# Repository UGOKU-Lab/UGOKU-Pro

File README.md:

# UGOKU One
UGOKU Pro のハードウェア設計データ（KiCADデータ）のリポジトリです。

UGOKU Pro はモータやセンサを使ったロボットなどのアプリケーションを少しでも手軽にテスト、制御することを目的に開発している汎用基板です。

広く普及しているマイコンボードや無線モジュールに加え、高出力なDCモータドライバを2個搭載しています。さらに、汎用IOポートを設け幅広いアプリケーションに対応します。
Androidアプリ[FlexConsole](https://github.com/UGOKU-Lab/FlexConsole_for_Bluetooth_Serial)と組み合わせることでスマートフォンから手軽に遠隔操作や監視が行えます。

[](

)

| 主要搭載部品 |  |
----|---- 
| マイコンボード | Nucleo-F303K8 | 
| 無線モジュール | ESP32-WROOM-32E |
| DCモータドライバ | 2× TB67H303HG |
| CANトランシーバ | MCP2562-E/SN |

# 使用ライブラリ
[SnapMagic](https://www.snapeda.com/home/) よりダウンロードしたKiCADのライブラリ（CC BY-SA）を使用しています

# ライセンス
<br />この データ は <a rel="license" href="http://creativecommons.org/licenses/by-sa/4.0/deed.ja">クリエイティブ・コモンズ 表示 4.0 国際 ライセンス</a>の下に提供されています。

本データおよび本データにより製作した基板は良識の範囲で自由に非営利、営利問わず使用できます。また、改変、再配布も可能です。
ただし、再配布の際には本リポジトリのリンクを掲載を希望します。（本プロジェクトの目的に即した改良についてはプルリクエストを歓迎します）。  
また、本データにより生じた損害等の一切の責任を負いかねますので、ご了承ください。

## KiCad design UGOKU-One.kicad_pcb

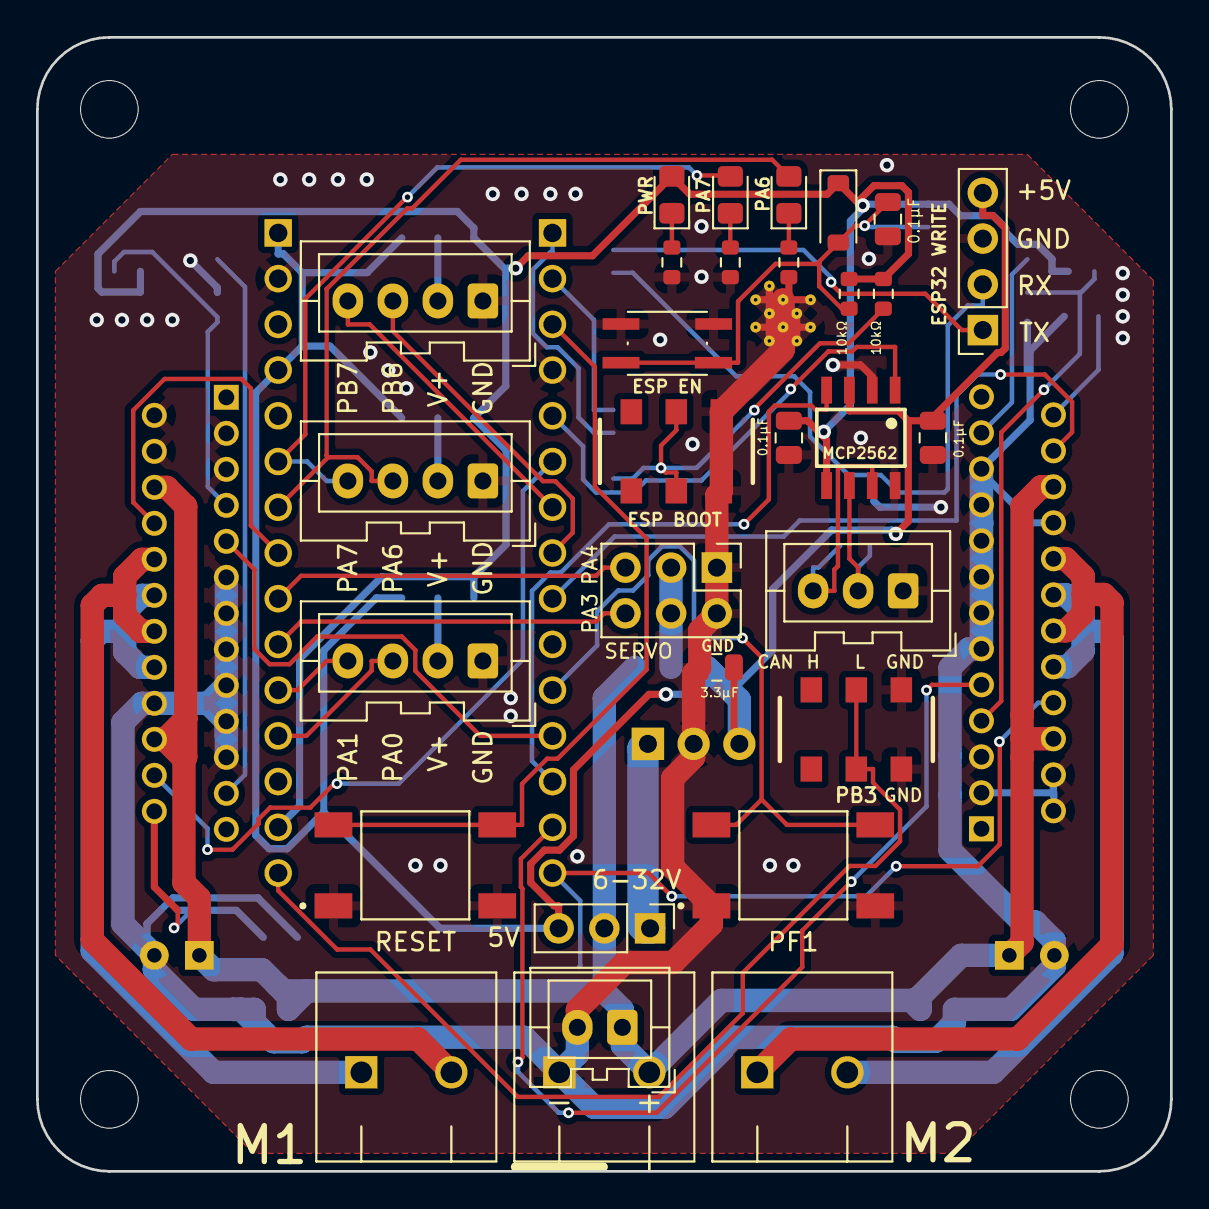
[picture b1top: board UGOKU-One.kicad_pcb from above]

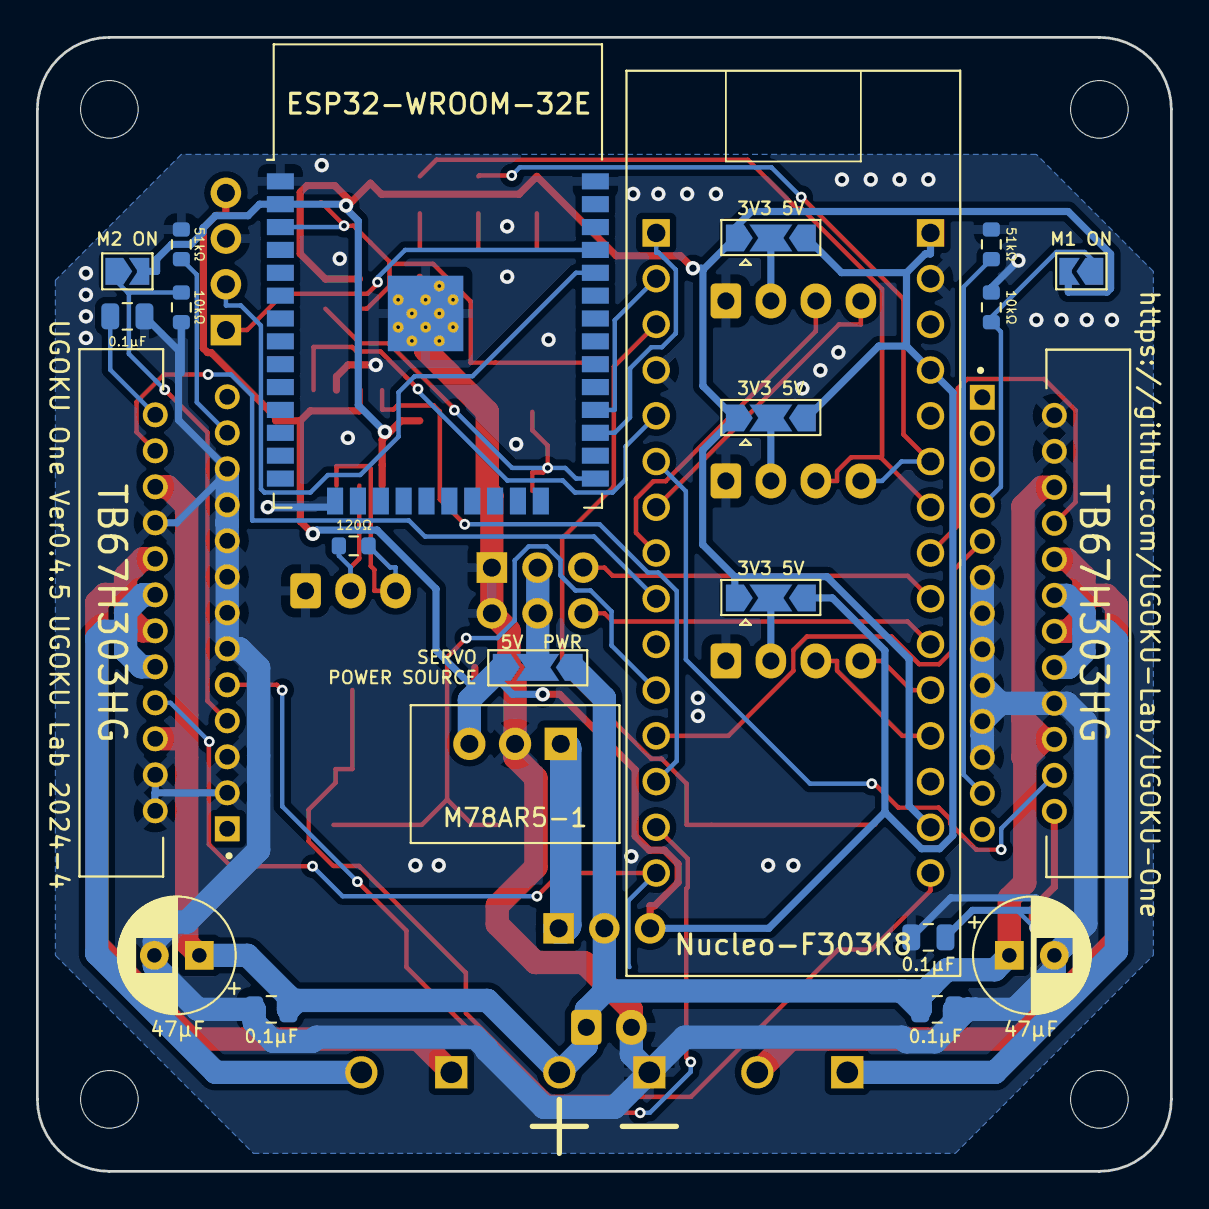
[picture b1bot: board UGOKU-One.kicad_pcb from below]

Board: 2 copper layers, 63.0 x 63.0 mm, 56 parts (22 on the bottom side), 49 nets.

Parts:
C1, C2, C3, C4, C9, C11, C13: 0.1μF; C_0805_2012Metric
C5, C12: 47μF; CP_Radial_D6.3mm_P2.50mm
C10: 3.3μF; C_0805_2012Metric
CN1, CN2, CN3: Conn_01x04; JST_XA_B04B-XASK-1_1x04_P2.50mm_Vertical
CN4: CAN; JST_XA_B03B-XASK-1_1x03_P2.50mm_Vertical
D1: D; D_SOD-123
J2: Conn_02x03_Odd_Even; PinHeader_2x03_P2.54mm_Vertical
J3: Conn_01x02_Male; JST_XA_B02B-XASK-1_1x02_P2.50mm_Vertical
J4: PA10; PinHeader_1x03_P2.54mm_Vertical
J6: Conn_01x04; PinSocket_1x04_P2.54mm_Vertical
JP1, JP2, JP3, JP4: Jumper_NC_Dual; SolderJumper-3_P2.0mm_Open_TrianglePad1.0x1.5mm
L1: PWR; LED_0805_2012Metric_Pad1.15x1.40mm_HandSolder
L2, L3: LED; LED_0805_2012Metric_Pad1.15x1.40mm_HandSolder
MH1, MH2, MH3, MH4: MountingHole_3.2mm_M3
MJP1, MJP2: Jumper; SolderJumper-2_P1.3mm_Open_TrianglePad1.0x1.5mm
R1: 120Ω; R_0603_1608Metric
R2, R3: 10kΩ; R_0603_1608Metric
R4, R5, R6: 3.3k; R_0603_1608Metric
R7, R13: 51kΩ; R_0603_1608Metric
R9, R12: 10k; R_0603_1608Metric
SW1: PF1; SW_TL3301FF160QG
SW2: RESET; SW_TL3301FF160QG
SW3, SW5: SW_Push_DPDT; SSSS213202
SW4: SW_Push_1P1T_NO_Vertical_Wuerth_434133025816
T1, T2, T3: PTS_1.5_2
U1: M78AR5-1; M78AR
U2: NUCLEO-F303K8; MODULE_NUCLEO-F303K8
U4, U5: TB67H303HG; TO100P2930X465X1937-25
U6: MCP2562-E_SN; SOIC127P600X175-8N
U7: ESP32-WROOM-32

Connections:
+3V3: C2.1, D1.1 (K), JP1.1, JP2.1, JP3.1, L1.2 (A), MJP1.2, MJP2.2, R9.2, R12.2, U2.4_14 (+3V3), U6.5 (VIO), U7.2 (VDD)
+5V: C1.1, C10.1, J4.3, J6.4, JP1.3, JP2.3, JP3.3, JP4.3, U1.3 (Vout), U2.4_1 (VIN), U2.4_4 (+5V), U6.3 (VDD)
GND: C1.2, C2.2, C3.2, C4.2, C5.2, C9.2, C10.2, C11.2, C12.2, C13.2, CN1.1, CN2.1, CN3.1, CN4.1, J2.1, J2.2, J3.2, J6.3, R2.1, R3.1, R4.1, R5.1, R6.1, R7.2, R13.2, SW1.1, SW2.1, SW3.3 (C), SW3.6 (C), SW4.1, SW5.3 (C), SW5.6 (C), T3.P$1, U1.2 (GND), U2.3_4 (GND_1), U2.4_2 (GND_2), U4.2 (SGND), U4.3 (SELECT), U4.4 (TEST1), U4.5 (VREF), U4.11 (RSB), U4.13 (PGNDB), U4.15 (RSA), U4.17 (PGNDA), U4.18 (TEST2), U4.19 (TEST3), U4.21 (TEST4), U5.2 (SGND), U5.3 (SELECT), U5.4 (TEST1), U5.5 (VREF), U5.11 (RSB), U5.13 (PGNDB), U5.15 (RSA), U5.17 (PGNDA), U5.18 (TEST2), U5.19 (TEST3), U5.21 (TEST4), U6.2 (VSS), U6.8 (STBY), U7.1 (GND), U7.15 (GND), U7.38 (GND), U7.39 (GND)
unnamed: CN1.2, JP3.2
unnamed: CN1.3, U2.3_8 (PB6)
unnamed: CN1.4, U2.3_7 (PB7)
unnamed: CN2.2, JP2.2
unnamed: CN2.3, L3.2 (A), U2.4_7 (PA6)
unnamed: CN2.4, L2.2 (A), U2.4_6 (PA7)
unnamed: CN3.2, JP1.2
unnamed: CN3.3, U2.4_12 (PA0)
unnamed: CN3.4, U2.4_11 (PA1)
unnamed: CN4.2, R1.1, U6.6 (CANL)
unnamed: CN4.3, R1.2, U6.7 (CANH)
unnamed: C9.1, D1.2 (A), R9.1, SW4.2, U7.3 (EN)
unnamed: J2.3, J2.4, JP4.2
unnamed: J2.5, U2.4_9 (PA4)
unnamed: J2.6, U2.4_10 (PA3)
unnamed: J4.1, U1.1 (Vin)
unnamed: J6.1, U7.35 (TXD0/IO1)
unnamed: J6.2, U7.34 (RXD0/IO3)
unnamed: L1.1 (K), R4.2
unnamed: L2.1 (K), R5.2
unnamed: L3.1 (K), R6.2
unnamed: SW2.2, U2.3_3 (NRST_1)
unnamed: U2.3_12 (PA8), U5.9 (IN2)
unnamed: U2.3_1 (PA9), U7.27 (IO16)
unnamed: U2.3_2 (PA10), U7.28 (IO17)
unnamed: U2.3_13 (PA11), U6.4 (RXD)
unnamed: U2.3_5 (PA12), U6.1 (TXD)
unnamed: U2.3_6 (PB0), U5.22 (PWM)
unnamed: U2.3_9 (PB1), U4.22 (PWM)
unnamed: U2.3_15 (PB4), U4.8 (IN1)
unnamed: U2.3_14 (PB5), U4.9 (IN2)
unnamed: SW1.2, U2.3_11 (PF1)
unnamed: U2.4_8 (PA5), U5.8 (IN1)
unnamed: SW5.2 (B), SW5.5 (B), U2.4_15 (PB3)
unnamed: R13.1, U4.23 (OSC)
unnamed: T2.P$1, U4.12 (OUT1B), U4.16 (OUT1A)
unnamed: T2.P$2, U4.10 (OUT2B), U4.14 (OUT2A)
unnamed: MJP1.1, R2.2, U4.7 (STBY)
unnamed: C13.1, U4.24 (VREG)
unnamed: R7.1, U5.23 (OSC)
unnamed: T1.P$1, U5.12 (OUT1B), U5.16 (OUT1A)
unnamed: T1.P$2, U5.10 (OUT2B), U5.14 (OUT2A)
unnamed: MJP2.1, R3.2, U5.7 (STBY)
unnamed: C3.1, U5.24 (VREG)
unnamed: R12.1, SW3.2 (B), SW3.5 (B), U7.25 (IO0)
PWR: C4.1, C5.1, C11.1, C12.1, J3.1, J4.2, JP4.1, T3.P$2, U4.6 (VCC), U4.20 (VCC), U5.6 (VCC), U5.20 (VCC)

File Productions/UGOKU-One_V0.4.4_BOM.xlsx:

Comment | Designator | Footprint | JLCPCB Part #（optional）
100nF | C1, C11, C13, C2, C3, C4, C9 | C0805 | C1711
3.3uF | C10 | C0805 | C2182175
47uF | C5,C12 |  | C106665
51k | R13, R7 | R0603
10k | R2, R3, R12, R9 | R0603
120 | R1 | R0603 | C2906988
510 | R4 | R0603 | C965132
1k | R5, R6 | R0603
LED | L1 | L0805 | C264427
LED | L2, L3 | L0805 | C84256
DIODE | D1 | SOD-123 | C8598
SSSS213202 | SW3, SW5 |  | C115375
TL3301FF160QG | SW1, SW2 |  | C273522
SKRPABE010 | SW4 |  | C115360
MCP2562-E/SN | U6 | SOIC127P600X175-8N | C53609
ESP32-WROOM-32E-N16 | U7 |  | C701343
TB67H303HG | U4,U5 |  | C1556864
1792863 | T1,T2,T3 |  | C3032345
PIN-HEADER-3P | J4 |  | C2937625
B03B-XASK-1(LF)(SN) | CN4 |  | C265055
B04B-XASK-1(LF)(SN) | CN1,CN2,CN3 |  | C264994
A2541HWV-4P | J6 |  | C5176037
PZ254V-12-6P | J2 |  | C492420
B-2200S15P-A120 | P1,P2 |  | C124408

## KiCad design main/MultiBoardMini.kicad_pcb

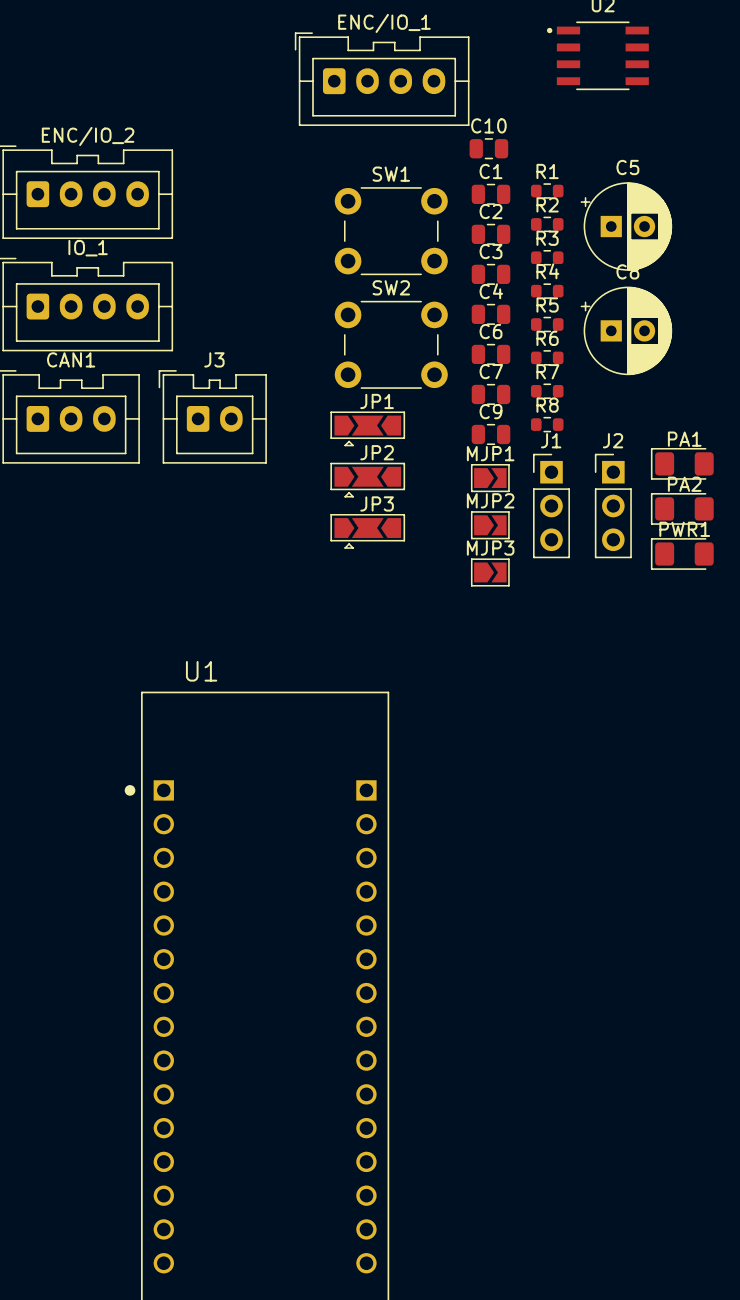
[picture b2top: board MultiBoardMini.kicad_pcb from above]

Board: 2 copper layers, 38 parts (0 on the bottom side), 24 nets, no tracks yet.

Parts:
C1, C2, C4, C7, C10: 0.1μF; C_0805_2012Metric
C3, C6: 0.1uF; C_0805_2012Metric
C5, C8: 47μF; CP_Radial_D6.3mm_P2.50mm
C9: 4.7μF; C_0805_2012Metric
CAN1: CAN; JST_XA_B03B-XASK-1_1x03_P2.50mm_Vertical
ENC/IO_1, ENC/IO_2: Conn_01x04; JST_XA_B04B-XASK-1_1x04_P2.50mm_Vertical
IO_1: Conn_01x04; JST_XA_B04B-XASK-1_1x04_P2.50mm_Vertical
J1: PB0; PinHeader_1x03_P2.54mm_Vertical
J2: PA10; PinHeader_1x03_P2.54mm_Vertical
J3: Conn_01x02_Male; JST_XA_B02B-XASK-1_1x02_P2.50mm_Vertical
JP1, JP2, JP3: Jumper_NC_Dual; SolderJumper-3_P2.0mm_Open_TrianglePad1.0x1.5mm
MJP1, MJP2, MJP3: Jumper; SolderJumper-2_P1.3mm_Open_TrianglePad1.0x1.5mm
PA1, PA2: LED; LED_1206_3216Metric_Pad1.42x1.75mm_HandSolder
PWR1: PWR; LED_1206_3216Metric_Pad1.42x1.75mm_HandSolder
R1: 120Ω; R_0603_1608Metric
R2, R7: 10kΩ; R_0603_1608Metric
R3, R8: 51kΩ; R_0603_1608Metric
R4, R5, R6: 3.3k; R_0603_1608Metric
SW1: PF1; SW_PUSH_6mm_H4.3mm
SW2: RESET; SW_PUSH_6mm_H4.3mm
U1: NUCLEO-F303K8; MODULE_NUCLEO-F303K8
U2: SOIC127P600X175-8N

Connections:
+3V3: C1.1, JP1.1, JP2.1, JP3.1, MJP1.2, MJP2.2, PWR1.2 (A), U1.4_14 (+3V3), U2.5 (VIO)
+5V: C2.1, C9.1, C10.1, JP1.3, JP2.3, JP3.3, MJP3.1, U1.4_1 (VIN), U1.4_4 (+5V), U2.3 (VDD)
GND: C1.2, C2.2, C3.2, C4.2, C5.2, C6.2, C7.2, C8.2, C9.2, C10.2, CAN1.1, ENC/IO_1.1, ENC/IO_2.1, IO_1.1, J1.1, J2.1, J3.2, R2.1, R3.1, R4.1, R5.1, R6.1, R7.1, R8.1, SW1.1, SW2.1, U1.3_4 (GND_1), U1.4_2 (GND_2), U2.2 (VSS)
unnamed: ENC/IO_1.2, JP1.2
unnamed: ENC/IO_1.3, U1.4_12 (PA0)
unnamed: ENC/IO_1.4, U1.4_11 (PA1)
unnamed: ENC/IO_2.2, JP2.2
unnamed: ENC/IO_2.3, IO_1.4, PA2.2 (A), U1.4_7 (PA6)
unnamed: ENC/IO_2.4, PA1.2 (A), U1.4_6 (PA7)
unnamed: IO_1.2, JP3.2
unnamed: IO_1.3, U1.4_8 (PA5)
unnamed: J1.3, U1.3_6 (PB0)
unnamed: PA1.1 (K), R5.2
unnamed: PA2.1 (K), R6.2
unnamed: PWR1.1 (K), R4.2
unnamed: MJP1.1, R2.2
unnamed: MJP2.1, R7.2
unnamed: SW2.2, U1.3_3 (NRST_1)
unnamed: U1.3_13 (PA11), U2.4 (RXD)
unnamed: U1.3_5 (PA12), U2.1 (TXD)
unnamed: SW1.2, U1.3_11 (PF1)
unnamed: R1.2, U2.7 (CANH)
unnamed: R1.1, U2.6 (CANL)
PWR: C4.1, C5.1, C7.1, C8.1, J1.2, J2.2, J3.1

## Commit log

2023-09-30 Add files via upload
    initial commit
2023-10-01 回路図にESP32モジュール追加
2023-10-02 ESP32モジュールのライブラリを追加
2023-10-03 Update LICENSE
    Change CC to BY-SA
2023-10-08 change Libraries path, update design
2023-10-08 update Library path setting, design
2023-10-21 update sch
2023-10-22 add slide switch footprints
2023-10-22 ERC実行に伴うエラーの解消 ・CANコネクタの接続ができていなかったので接続した。 ・モータドライバのライブラリのIO特性が設定されていないせいでエラーが出ていたが、問題ないとして除外項目に追加した。
2023-10-22 Update iroiro
2023-10-22 部品は一おおむね完了
2023-10-22 PWR MOT 配線一旦できた
2023-10-22 MOT PWR 修正
2023-10-22 自動配線前のいろいろごにょごにょしたやつ
2023-10-22 オートルート前のほぼ完成
2023-10-22 Autoroute 前の完成だと思われるもの
2023-10-22 配線一応できた
2023-10-22 配線一応完了 DRC確認済み
2023-10-22 ほぼ完成みたいなもの
2023-10-24 緊急発注用
2023-11-11 改良版の電源配線暫定版
2023-11-11 ESP大型化のためつめつめ
2023-11-12 esp32変更
2023-11-23 回路図 ESP32の回路修正完了
2023-11-25 toriaezu
2023-11-25 手動配線完成
2023-11-25 MOT配線見直し
2023-11-25 MDGND配線見直し
2023-11-25 配線完成
2023-11-25 ほぼ完成
2023-11-26 V0.41試作発注用完成 PCB ASSEMBLY用BOM、positionデータ追加
2023-11-26 とりあえず保存
2023-12-09 Update README.md
    make public annoucement
2024-01-03 GNDと5V+がつながっていた問題を解消
2024-01-05 回路図変更
2024-01-05 ESPとNucleoが接続されてなかったので接続
2024-01-06 Change Project name
2024-01-06 Change name 再び
2024-01-07 2024/1/6発注仕様
2024-01-20 Update README.md
    Add description
2024-01-21 Via size modified to match JLCPCB rules
2024-01-29 Motor driver STM pin assignment replacement
2024-01-29 Motor driver STM pin assignment replacement completed
2024-01-29 add description of library
2024-02-10 update silk version
2024-02-22 Update Diode footprint and servo pin header
2024-03-01 XA使用Verの最終版
2024-03-02 IOコネクタを圧着不要コネクタhar-flexicon化する検討を開始
2024-03-03 V0.4.4 2024-3-3 発注仕様
2024-03-15 saisinban(XA仕様)
2024-03-31 Modify ESP32 position
2024-03-31 save
2025-05-18 change name README

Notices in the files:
README.md:
CC BY-SA 4.0
